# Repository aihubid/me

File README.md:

# <h3>Welcome to IOSHUB Repository</h3>
This repository is my works-archieve as coder and electronic hobbyist from 1987 to 2019.

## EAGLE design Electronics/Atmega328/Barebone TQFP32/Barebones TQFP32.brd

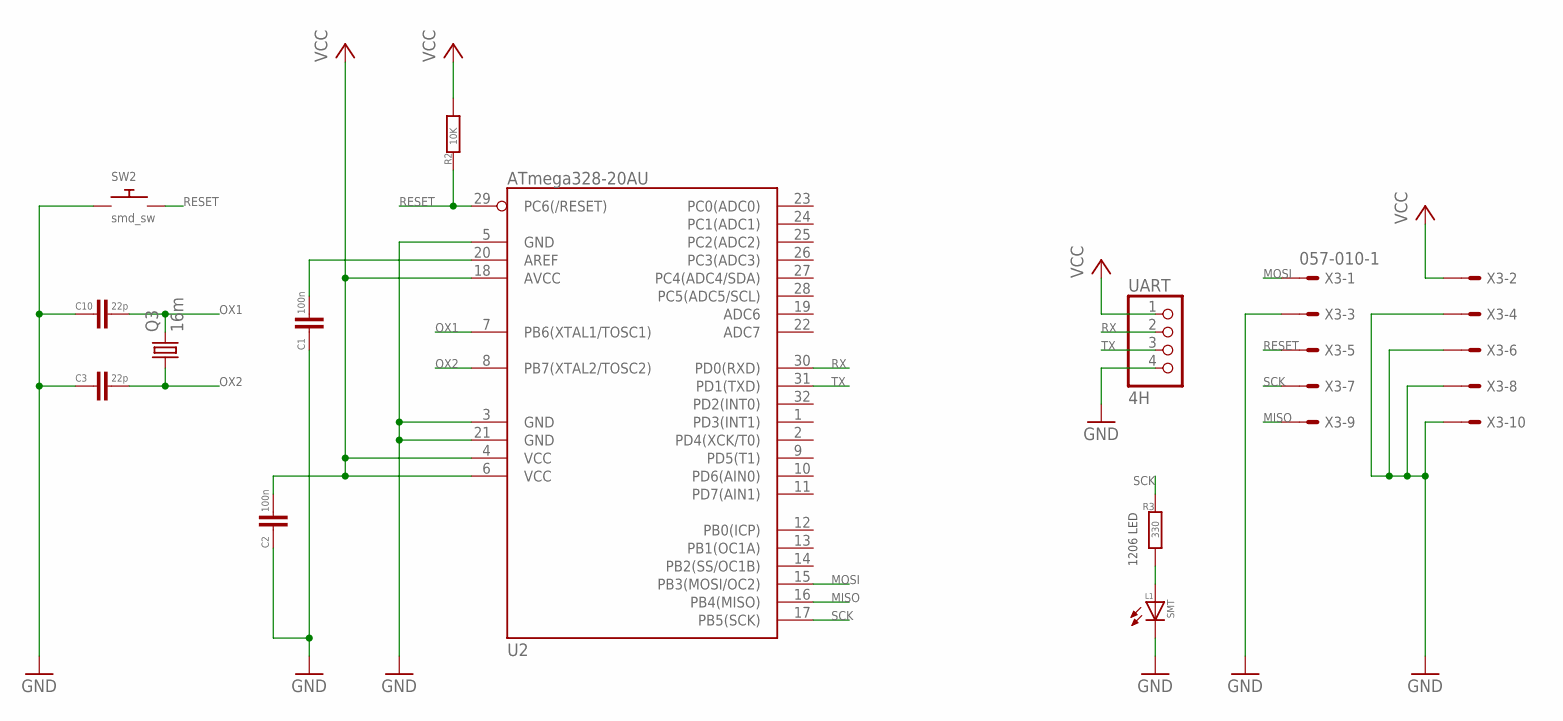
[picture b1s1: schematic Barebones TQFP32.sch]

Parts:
C1, C2: 100n; C1206
C3, C10: 22p; C1206
L1: SMT; 1206
Q3: 16m; HC49UP
R2: 10K; R1206
R3: 330; R1206
SW2: smd_sw; TACT_PANA-EVQ
U2: ATmega328-20AU; TQFP32
UART: 4H; 1X04
X3: 057-010-1

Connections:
GND: C1.1, C2.1, C3.1, C10.1, L1.C, SW2.P$1, U2.3 (GND), U2.5 (GND), U2.21 (GND), UART.4, X3.3, X3.4, X3.6, X3.8, X3.10
MISO: U2.16 (PB4(MISO)), X3.9
MOSI: U2.15 (PB3(MOSI/OC2)), X3.1
unnamed: C1.2, U2.20 (AREF)
unnamed: L1.A, R3.2
OX1: C10.2, Q3.2, U2.7 (PB6(XTAL1/TOSC1))
OX2: C3.2, Q3.1, U2.8 (PB7(XTAL2/TOSC2))
RESET: R2.1, SW2.P$2, U2.29 (PC6(/RESET)), X3.5
RX: U2.30 (PD0(RXD)), UART.2
SCK: R3.1, U2.17 (PB5(SCK)), X3.7
TX: U2.31 (PD1(TXD)), UART.3
VCC: C2.2, R2.2, U2.4 (VCC), U2.6 (VCC), U2.18 (AVCC), UART.1, X3.2

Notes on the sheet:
1206 LED

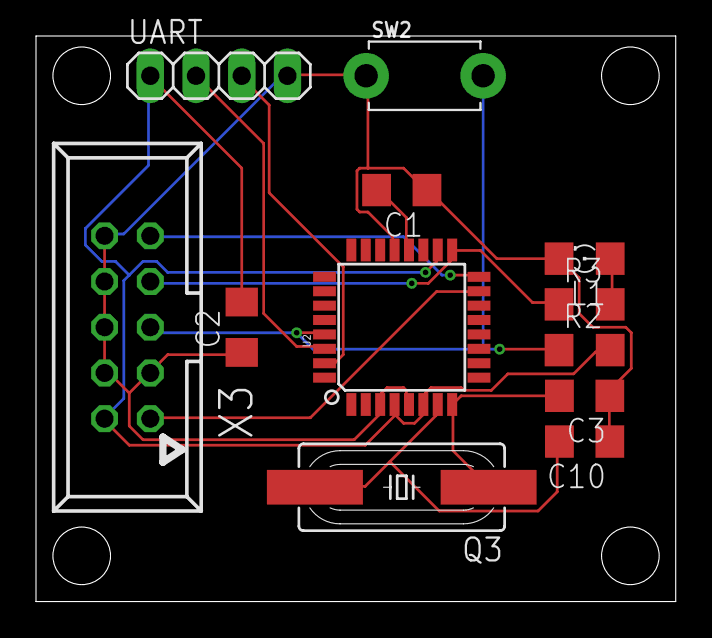
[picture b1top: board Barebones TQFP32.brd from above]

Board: 2 copper layers, 35.5 x 31.4 mm, 12 parts (0 on the bottom side), 12 nets.

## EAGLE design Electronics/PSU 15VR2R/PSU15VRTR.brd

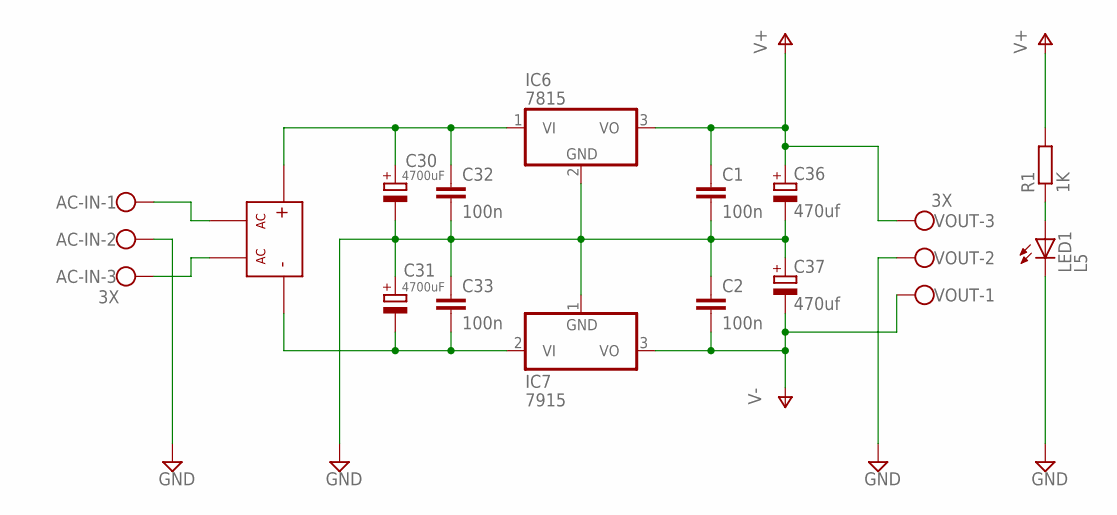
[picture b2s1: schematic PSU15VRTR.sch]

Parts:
AC-IN: 3X; W237-103
C1, C2, C32, C33: 100n; C050-025X075
C30, C31: 4700uF; E7,5-18
C36, C37: 470uf; E3,5-8
IC6: 7815; TO220H
IC7: 7915; TO220H
LED1: L5; LED5MM
R1: 1K; 0204/7
REC1: RECTIFIER
VOUT: 3X; W237-103

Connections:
AC1: AC-IN.1, REC1.AC1
AC2: AC-IN.3, REC1.AC0
GND: AC-IN.2, C1.2, C2.1, C30.-, C31.+, C32.2, C33.1, C36.-, C37.+, IC6.2 (GND), IC7.1 (GND), LED1.K (C), VOUT.2
unnamed: LED1.A, R1.1
unnamed: C30.+, C32.1, IC6.1 (VI), REC1.P
unnamed: C31.-, C33.2, IC7.2 (VI), REC1.N
V+: C1.1, C36.+, IC6.3 (VO), R1.2, VOUT.3
V-: C2.2, C37.-, IC7.3 (VO), VOUT.1

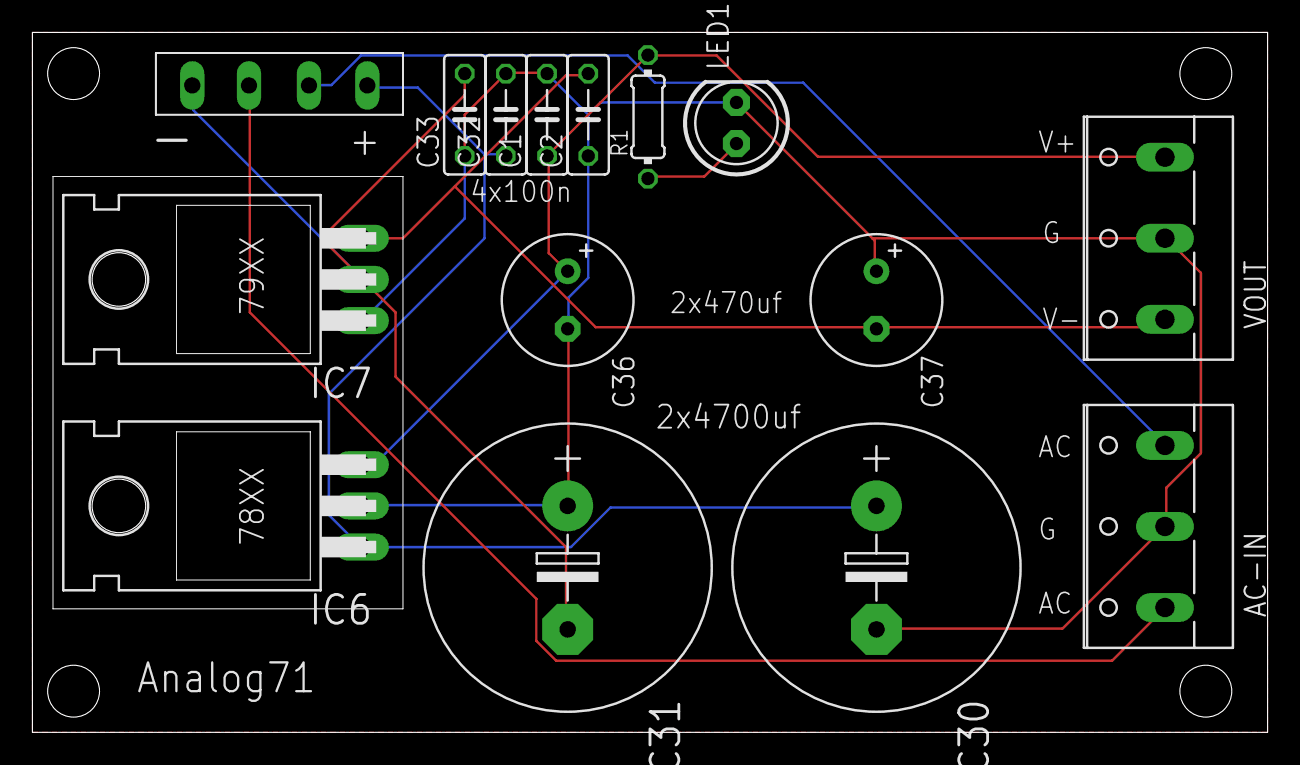
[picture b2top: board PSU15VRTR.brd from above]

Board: 2 copper layers, 76.2 x 43.2 mm, 15 parts (0 on the bottom side), 8 nets.

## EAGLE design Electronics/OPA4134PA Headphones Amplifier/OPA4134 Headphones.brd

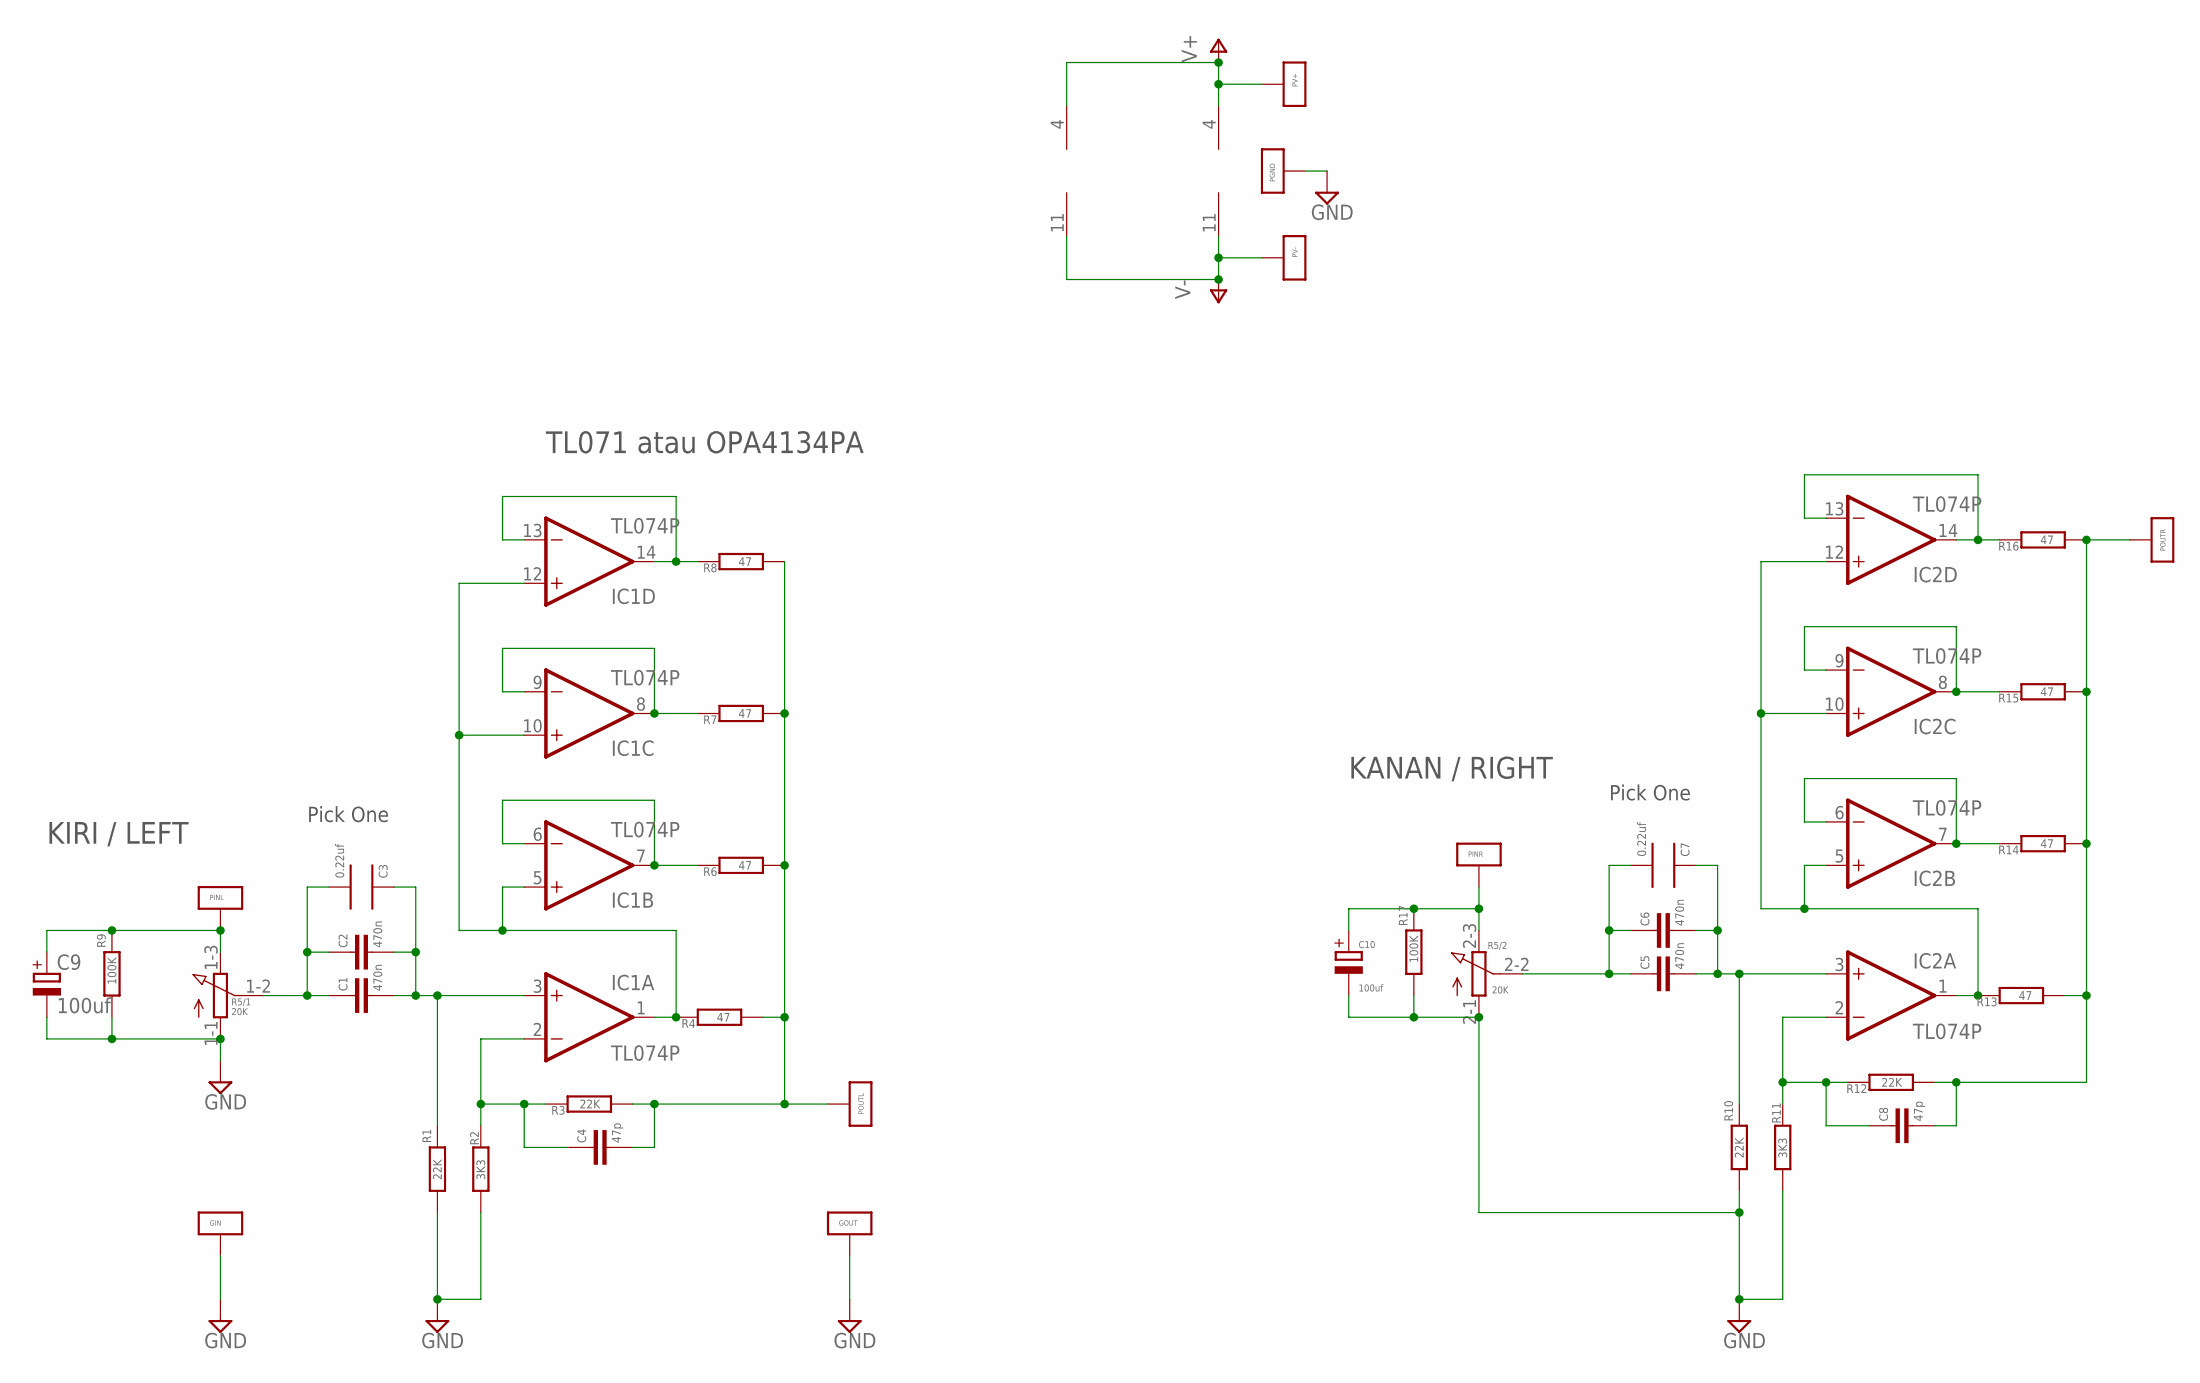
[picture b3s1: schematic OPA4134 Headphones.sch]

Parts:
C1, C5: 470n; C050-025X075
C2, C6: 470n; C102-054X133
C3, C7: 0.22uf; BENICCAP
C4, C8: 47p; C050-025X075
C9, C10: 100uf; E2,5-7
GIN: PIN-BIG1X; PIN-BIG
GOUT: PIN-BIG1X; PIN-BIG
IC1, IC2: TL074P; DIL14
PGND: PIN-BIG1X; PIN-BIG
PINL: PIN-BIG1X; PIN-BIG
PINR: PIN-BIG1X; PIN-BIG
POUTL: PIN-BIG1X; PIN-BIG
POUTR: PIN-BIG1X; PIN-BIG
PV+: PIN-BIG1X; PIN-BIG
PV-: PIN-BIG1X; PIN-BIG
R1, R3, R10, R12: 22K; 0204/7
R2, R11: 3K3; 0204/7
R4, R6, R7, R8, R13, R14, R15, R16: 47; 0204/7
R5: 20K; 3RP/1610G
R9, R17: 100K; 0204/7

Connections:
GND: C9.-, C10.-, GIN.P$1, GOUT.P$1, PGND.P$1, R1.1, R2.1, R5.1-1 (A), R5.2-1 (A), R9.1, R10.1, R11.1, R17.1
unnamed: C1.1, C2.1, C3.PIN1, R5.1-2 (S)
unnamed: C1.2, C2.2, C3.PIN2, IC1.3 (+IN), R1.2
unnamed: IC1.6 (-IN), IC1.7 (OUT), R6.2
unnamed: C4.1, IC1.2 (-IN), R2.2, R3.2
unnamed: IC1.1 (OUT), IC1.5 (+IN), IC1.10 (+IN), IC1.12 (+IN), R4.2
unnamed: C4.2, POUTL.P$1, R3.1, R4.1, R6.1, R7.1, R8.1
unnamed: C10.+, PINR.P$1, R5.2-3 (E), R17.2
unnamed: IC1.8 (OUT), IC1.9 (-IN), R7.2
unnamed: IC1.13 (-IN), IC1.14 (OUT), R8.2
unnamed: C5.1, C6.1, C7.PIN1, R5.2-2 (S)
unnamed: C5.2, C6.2, C7.PIN2, IC2.3 (+IN), R10.2
unnamed: C8.1, IC2.2 (-IN), R11.2, R12.2
unnamed: IC2.1 (OUT), IC2.5 (+IN), IC2.10 (+IN), IC2.12 (+IN), R13.2
unnamed: C8.2, POUTR.P$1, R12.1, R13.1, R14.1, R15.1, R16.1
unnamed: IC2.6 (-IN), IC2.7 (OUT), R14.2
unnamed: IC2.8 (OUT), IC2.9 (-IN), R15.2
unnamed: IC2.13 (-IN), IC2.14 (OUT), R16.2
unnamed: C9.+, PINL.P$1, R5.1-3 (E), R9.2
V+: IC1.4 (V+), IC2.4 (V+), PV+.P$1
V-: IC1.11 (V-), IC2.11 (V-), PV-.P$1

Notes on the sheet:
Pick One
KIRI / LEFT
KANAN / RIGHT
TL071 atau OPA4134PA

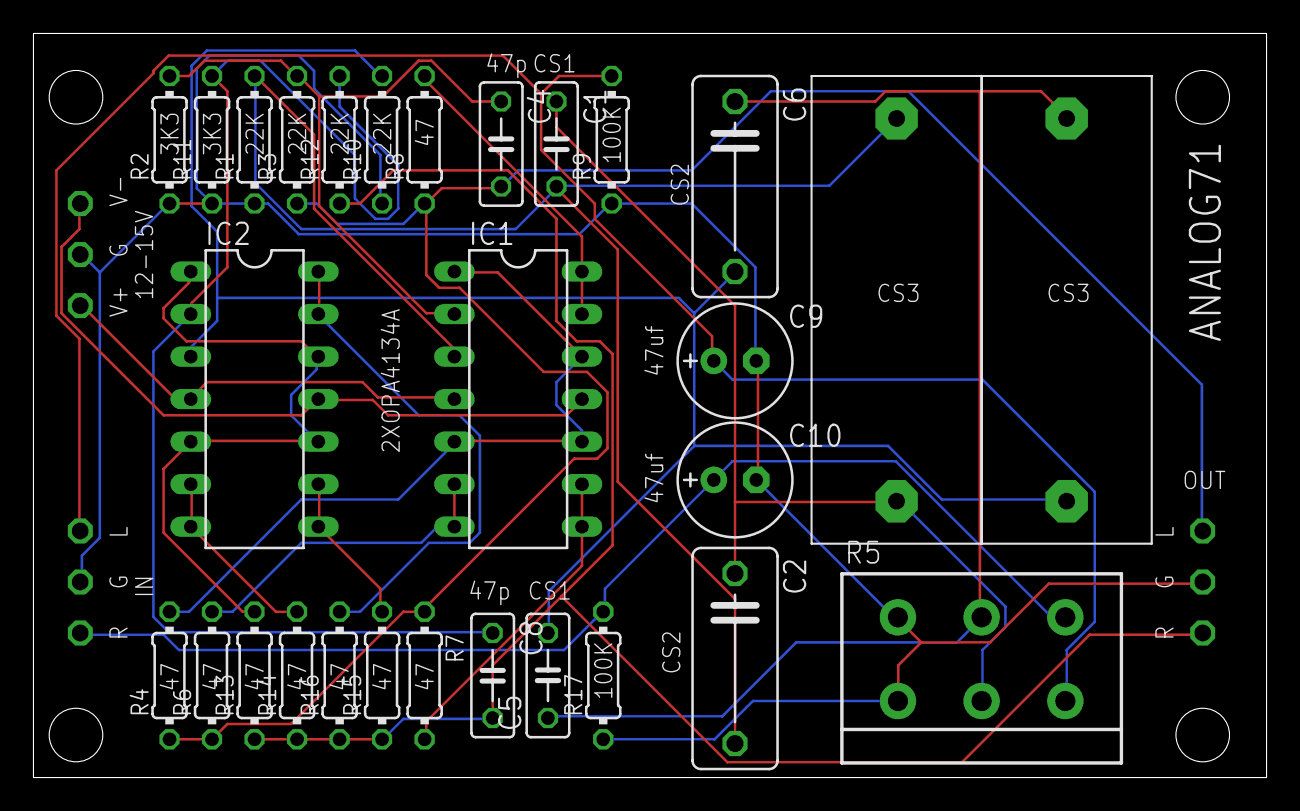
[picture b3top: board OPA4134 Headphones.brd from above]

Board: 2 copper layers, 73.7 x 44.5 mm, 38 parts (0 on the bottom side), 21 nets.

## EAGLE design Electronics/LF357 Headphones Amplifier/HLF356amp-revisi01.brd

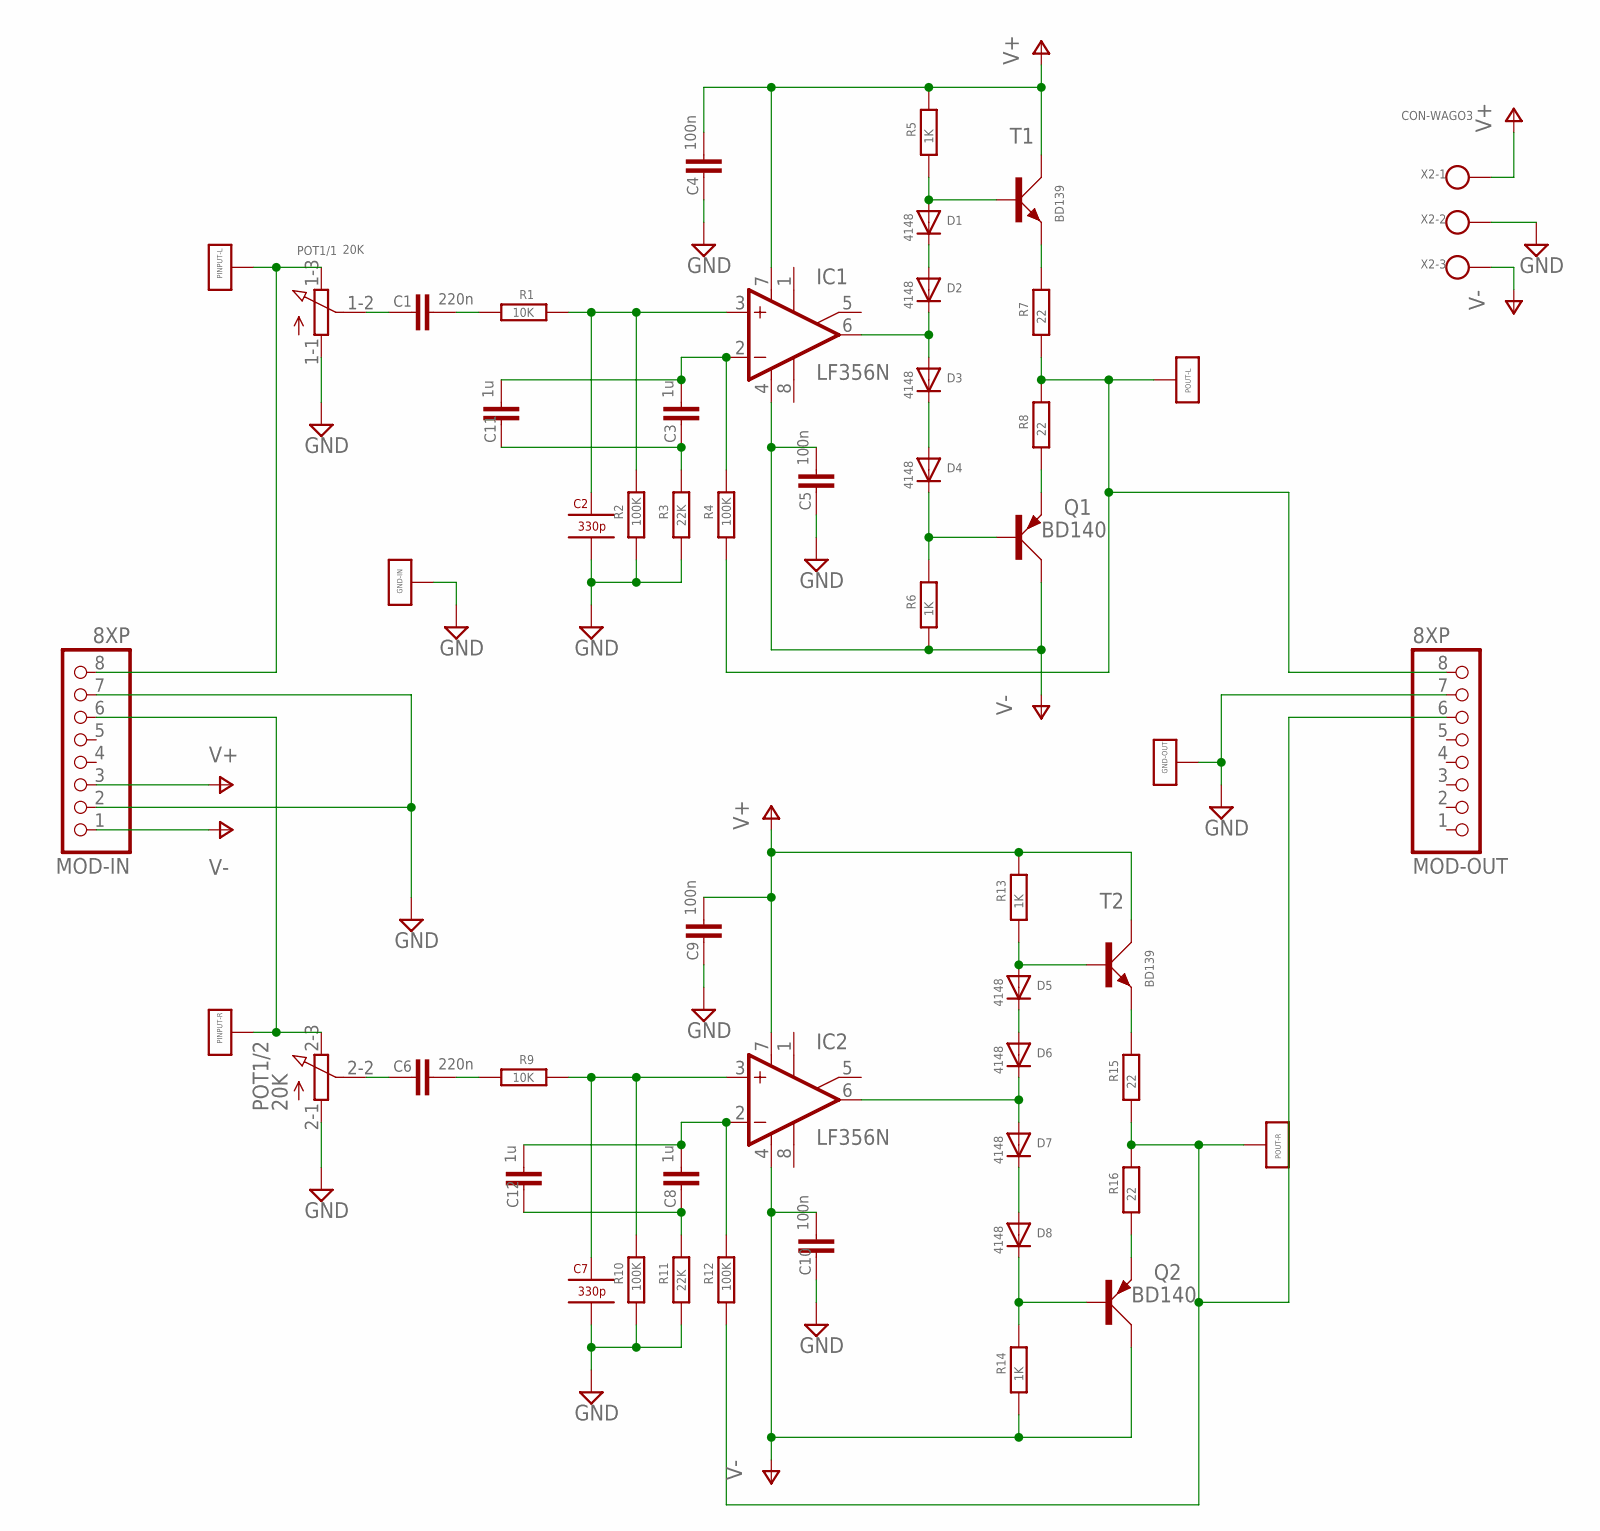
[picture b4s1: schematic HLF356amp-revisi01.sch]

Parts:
C1, C6: 220n; C050-025X075
C2, C7: 330p; RIFAEVOX
C3, C8: 1u; C150-072X183
C4, C5, C9, C10: 100n; C050-025X075
C11, C12: 1u; C050-075X075
D1, D2, D3, D4, D5, D6, D7, D8: 4148; DO35-7
GND-IN: PIN-BIG1X; PIN-BIG
GND-OUT: PIN-BIG1X; PIN-BIG
IC1, IC2: LF356N; DIL08
MOD-IN: 8XP; 1X08-BIG
MOD-OUT: 8XP; 1X08-BIG
PINPUT-L: PIN-BIG1X; PIN-BIG
PINPUT-R: PIN-BIG1X; PIN-BIG
POT1: 20K; 3RP/1610G
POUT-L: PIN-BIG1X; PIN-BIG
POUT-R: PIN-BIG1X; PIN-BIG
Q1, Q2: BD140; TO126AV
R1, R9: 10K; 0204/7
R2, R4, R10, R12: 100K; 0204/7
R3, R11: 22K; 0204/7
R5, R6, R13, R14: 1K; 0204/7
R7, R8, R15, R16: 22; 0204/7
T1, T2: BD139; TO126AV
X2: CON-WAGO3; W237-103

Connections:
AMP-INL: MOD-IN.8, PINPUT-L.P$1, POT1.1-3 (E)
AMP-INR: MOD-IN.6, PINPUT-R.P$1, POT1.2-3 (E)
AMP-OUTL: MOD-OUT.8, POUT-L.P$1, R4.1, R7.1, R8.2
AMP-OUTR: MOD-OUT.6, POUT-R.P$1, R12.1, R15.1, R16.2
B1: D1.A, R5.1, T1.B
B2: D4.C, Q1.B, R6.2
B3: D5.A, R13.1, T2.B
B4: D8.C, Q2.B, R14.2
E1: R7.2, T1.E
E2: Q1.E, R8.1
E3: R15.2, T2.E
E4: Q2.E, R16.1
GND: C2.P$2, C4.1, C5.1, C7.P$2, C9.1, C10.1, GND-IN.P$1, GND-OUT.P$1, MOD-IN.2, MOD-IN.7, MOD-OUT.7, POT1.1-1 (A), POT1.2-1 (A), R2.1, R3.1, R10.1, R11.1, X2.2
unnamed: C2.P$1, IC1.3 (+IN), R1.2, R2.2
unnamed: C1.2, R1.1
unnamed: C3.2, C11.2, IC1.2 (-IN), R4.2
unnamed: C3.1, C11.1, R3.2
unnamed: C1.1, POT1.1-2 (S)
unnamed: C7.P$1, IC2.3 (+IN), R9.2, R10.2
unnamed: D1.C, D2.A
unnamed: D2.C, D3.A, IC1.6 (OUT)
unnamed: D3.C, D4.A
unnamed: C6.2, R9.1
unnamed: C8.2, C12.2, IC2.2 (-IN), R12.2
unnamed: C8.1, C12.1, R11.2
unnamed: C6.1, POT1.2-2 (S)
unnamed: D5.C, D6.A
unnamed: D6.C, D7.A, IC2.6 (OUT)
unnamed: D7.C, D8.A
V+: C4.2, C9.2, IC1.7 (V+), IC2.7 (V+), MOD-IN.3, R5.2, R13.2, T1.C, T2.C, X2.1
V-: C5.2, C10.2, IC1.4 (V-), IC2.4 (V-), MOD-IN.1, Q1.C, Q2.C, R6.1, R14.1, X2.3

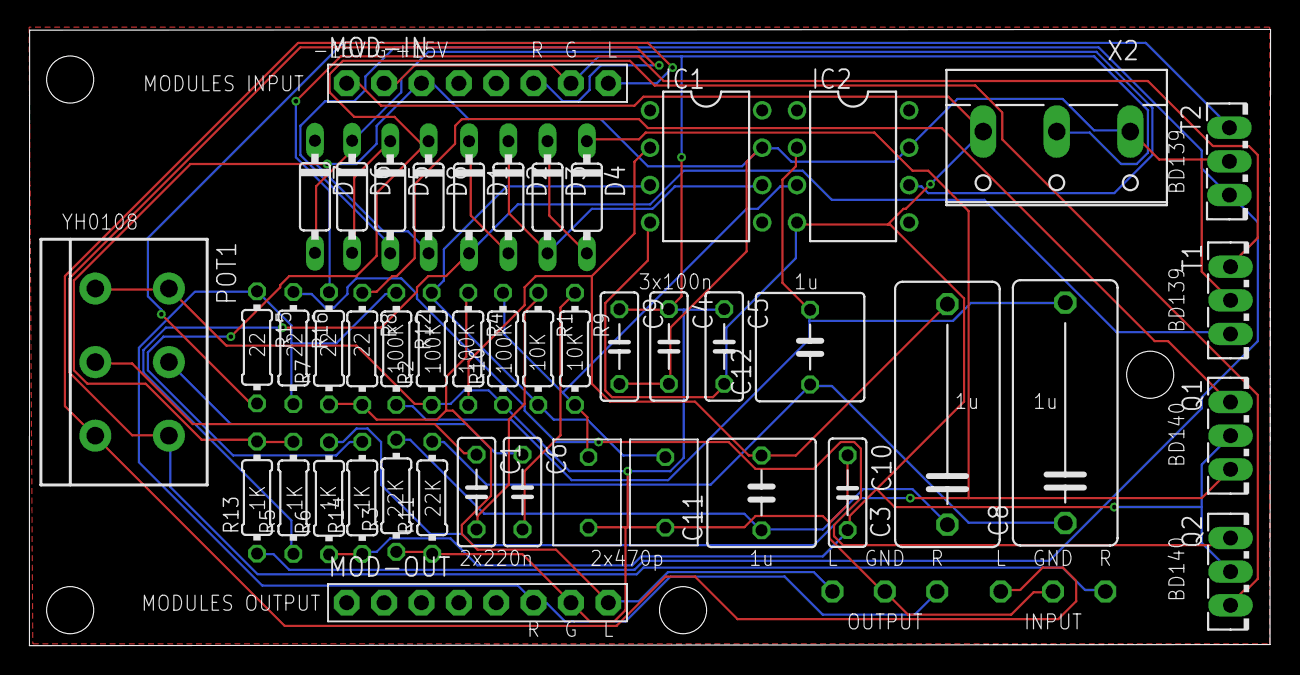
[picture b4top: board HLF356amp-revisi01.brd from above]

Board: 2 copper layers, 84.4 x 41.9 mm, 52 parts (0 on the bottom side), 31 nets.

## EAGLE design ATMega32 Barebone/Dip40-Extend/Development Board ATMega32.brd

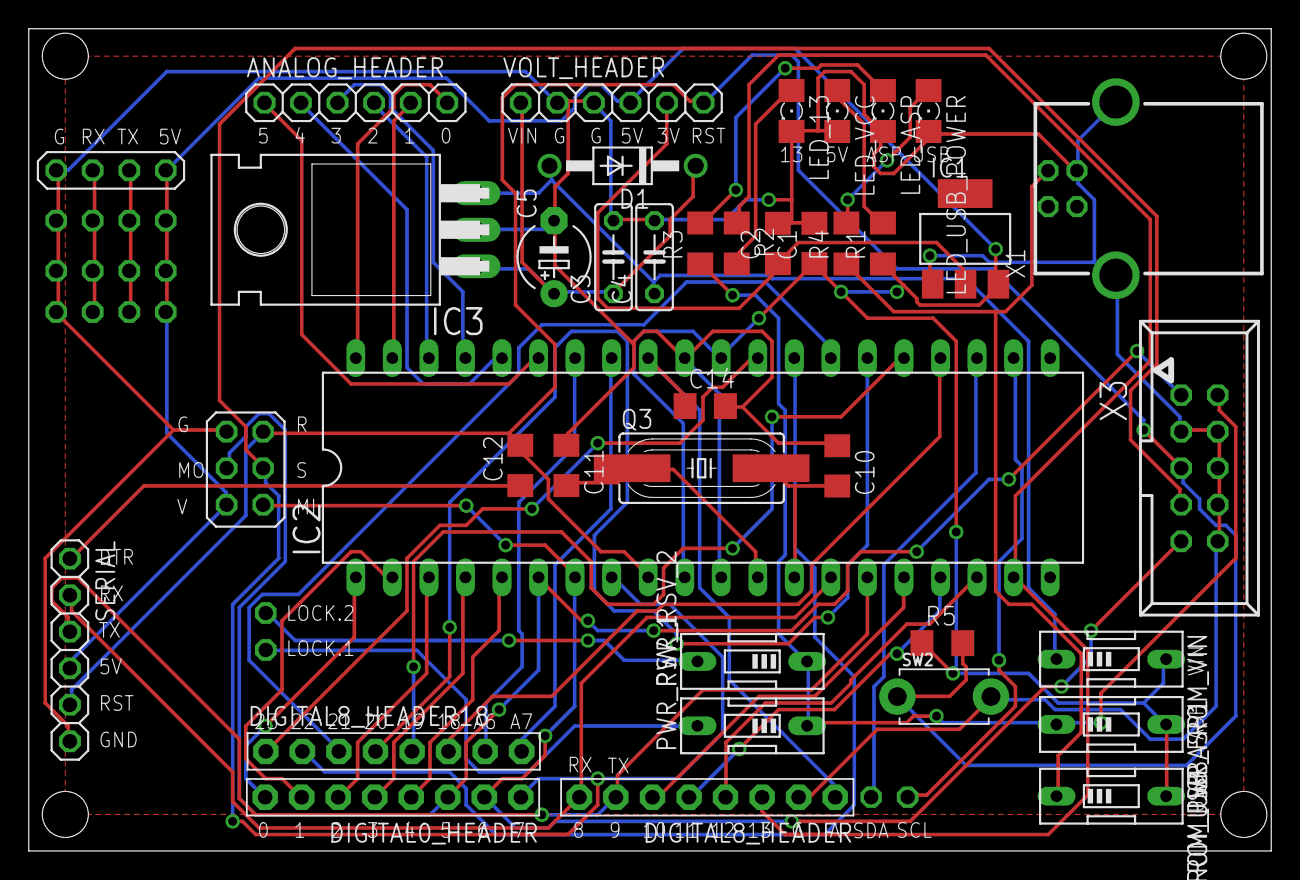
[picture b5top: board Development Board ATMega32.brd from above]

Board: 2 copper layers, 86.4 x 57.1 mm, 63 parts (0 on the bottom side), 50 nets.

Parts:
ANALOG_HEADER: h6; 1X06
C1, C2, C12, C14: 100n; C1206
C3, C4: 100n; C050-025X075
C5: 470u; E5-5
C10, C11: 22p; C1206
D1: 1N4004; DO41-10
DIGITAL0_HEADER, DIGITAL8_HEADER, DIGITAL8_HEADER18: h8; 1X08-BIG
IC1: REG1117; SOT223
IC2: MEGA32-P; DIL40
IC3: 7805T; TO220H
LED_13: SMT; 1206
LED_ASP: BLUE_SMT; 1206
LED_USB_POWER: SMT; 1206
LED_VCC: GREEN_SMT; 1206
P1, P2, P3, P4, P5, P6, P7, P8, P9, P10, P11, P12, P13, P14, P15, P16, P17, P18, P19, P20, P21, P22, P23, P24, P25, P26: PIN-BIG1X; PIN-BIG
PWR_FROM_USB: DIP_SW1; EDG-01
PWR_FROM_USBASP1: DIP_SW1; EDG-01
PWR_FROM_VIN: DIP_SW1; EDG-01
PWR_RSV_1, PWR_RSV_2: DIP_SW1; EDG-01
Q3: 16m; HC49UP
R1, R2, R3, R4: 1k; R1206
R5: 10K; R1206
SERIAL: 6H; 1X06
SW2: smd_sw; TACT_PANA-EVQ
VOLT_HEADER: h6; 1X06
X1: PN61729-S
X3: 057-010-1

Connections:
3V: C2.1, IC1.2, VOLT_HEADER.5
A0: ANALOG_HEADER.6, IC2.40
A1: ANALOG_HEADER.5, IC2.39
A2: ANALOG_HEADER.4, IC2.38
A3: ANALOG_HEADER.3, IC2.37
A4: ANALOG_HEADER.2, IC2.36
A5: ANALOG_HEADER.1, IC2.35
A6: DIGITAL8_HEADER18.7, IC2.34
A7: DIGITAL8_HEADER18.8, IC2.33
AREF: C14.1, DIGITAL8_HEADER.1, IC2.32
D0: DIGITAL0_HEADER.8, IC2.1
D1: DIGITAL0_HEADER.7, IC2.2
D2: DIGITAL0_HEADER.6, IC2.3
D3: DIGITAL0_HEADER.5, IC2.4
D4: DIGITAL0_HEADER.4, IC2.5
D10: DIGITAL8_HEADER.6, IC2.16
D11: DIGITAL8_HEADER.5, IC2.17
D12: DIGITAL8_HEADER.4, IC2.18
D13: DIGITAL8_HEADER.3, IC2.19, R2.1
D18: DIGITAL8_HEADER18.6, IC2.24
D19: DIGITAL8_HEADER18.5, IC2.25
D20: DIGITAL8_HEADER18.4, IC2.26
D21: DIGITAL8_HEADER18.3, IC2.27
D22: DIGITAL8_HEADER18.2, IC2.28
D23: DIGITAL8_HEADER18.1, IC2.29
DTR: C12.1, SERIAL.1
GND: C1.2, C2.2, C3.2, C4.2, C5.-, C10.1, C11.1, C14.2, DIGITAL8_HEADER.2, IC1.1, IC2.11, IC2.31, IC3.2, LED_13.C, LED_ASP.C, LED_USB_POWER.C, LED_VCC.C, P3.P$1, P13.P$1, P17.P$1, P20.P$1, P24.P$1, SERIAL.6, SW2.P$2, VOLT_HEADER.2, VOLT_HEADER.3, X1.4, X1.S1, X1.S2, X3.3, X3.4, X3.6, X3.8, X3.10
MISO: DIGITAL0_HEADER.2, IC2.7, P8.P$1, X3.9
MOSI: DIGITAL0_HEADER.3, IC2.6, P6.P$1, X3.1
unnamed: LED_VCC.A, R1.2
unnamed: LED_13.A, R2.2
unnamed: LED_ASP.A, R3.2
unnamed: PWR_FROM_USB.1, R4.1, X1.1
unnamed: LED_USB_POWER.A, R4.2
unnamed: C4.1, D1.A, IC3.3, PWR_FROM_VIN.1
unnamed: PWR_FROM_USBASP1.1, PWR_RSV_1.1, PWR_RSV_2.1, R3.1, X3.2
NEX_RX: P11.P$1, P15.P$1, P18.P$1, P22.P$1
NEX_TX: P12.P$1, P16.P$1, P19.P$1, P23.P$1
RESET: C12.2, IC2.9, P4.P$1, R5.2, SERIAL.5, SW2.P$1, VOLT_HEADER.6, X3.5
RSV1: P25.P$1, PWR_RSV_1.2
RSV2: P26.P$1, PWR_RSV_2.2
RX: DIGITAL8_HEADER.8, IC2.14, SERIAL.2
SCK: DIGITAL0_HEADER.1, IC2.8, P5.P$1, X3.7
SCL: IC2.22, P2.P$1
SDA: IC2.23, P1.P$1
TX: DIGITAL8_HEADER.7, IC2.15, SERIAL.3
VCC: C1.1, IC1.3, IC2.10, IC2.30, P7.P$1, P9.P$1, P10.P$1, P14.P$1, P21.P$1, PWR_FROM_USB.2, PWR_FROM_USBASP1.2, PWR_FROM_VIN.2, R1.1, R5.1, SERIAL.4, VOLT_HEADER.4
VIN: C3.1, C5.+, D1.C, IC3.1, VOLT_HEADER.1
X1_32: C10.2, IC2.13, Q3.2
X2_32: C11.2, IC2.12, Q3.1

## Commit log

2019-08-06 Add Atmega32 Barebone Eagle Schematic
2019-08-06 Create CNAME
2019-08-06 Deleting
2019-08-06 Add Atmega32 Barebone
2019-08-06 Delete
2019-08-06 Add Atmega 32 Barebone
2019-08-06 Reposition Folders
2019-08-06 Add Datasheets (mostly the components that i've used before)
